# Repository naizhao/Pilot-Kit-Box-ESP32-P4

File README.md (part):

# Pilot Kit Box (ESP32-P4 Edition)

<p align="center">
  <strong>开源低成本飞行数据盒子与态势感知设备 | Open-source low-cost flight data box and situational-awareness device</strong><br>
  官方网站 / Official website: <a href="https://air.club">air.club</a><br>
  网页刷机 / Web flasher: <a href="https://updater.pilotkit.app">updater.pilotkit.app</a>
</p>

**一块扩展板，一整套航空电子**：G1000 风格 PFD、360° 交通雷达、离线
航空地图（机场/导航台/FIX 叠加层）、航空电台收听与录音回放——中英
双语，无需联网；GDL90 数据经蓝牙与 Wi-Fi 对外输出，手机/EFB 无线直连。
**One expansion board, a full avionics suite**: a G1000-style PFD, a 360°
traffic radar, an offline aviation map (airports / navaids / fixes), and an
airband radio with recording playback — bilingual, offline, with GDL90 out
over both Bluetooth and Wi-Fi for phones and EFBs.

- 📶 **1090 + 978 + 航空电台 + GNSS，四路同时收**。SDR 方案只能盯一个频段，
  收了 ADS-B 就没有 UAT、听了电台就丢交通；这里每条链路一颗独立接收机，
  全部并发，互不抢占<br>
  **1090 + 978 + airband + GNSS, all receiving at once.** An SDR watches one
  band at a time — tune ADS-B, lose UAT; listen to the radio, drop traffic.
  Here every link has its own receiver, all concurrent, none blocked
- 📻 **航空电台（118–137 MHz）收听 + 录音回放**。塔台、进近、ATIS、CTAF
  直接出声；飞行中没听清的复述，落地回放重听<br>
  **Airband radio (118–137 MHz) with recording playback.** Tower, approach,
  ATIS and CTAF out loud; replay anything you missed on the ground
- 🧭 **全传感器套装，手持 GPS 都未必有**：IMU 姿态（PFD 地平仪）、气压
  高度与升降率、磁力计、**GPS/北斗/GLONASS/Galileo 四星座 GNSS**
  （内置陶瓷天线 + 外接可切）<br>
  **Full sensor suite, beyond most handheld GPSs**: IMU attitude (PFD
  horizon), barometric altitude and vertical speed, magnetometer, and
  **4-constellation GNSS (GPS/BeiDou/GLONASS/Galileo)** with switchable
  internal patch / external antenna
- 📡 所有数据来自无线电波与板载传感器，实时、真实、零联网——屏幕上的
  每一架飞机、每一条跑道、每一段通话都是本机直接接收解出来的，不是任何
  网络 API 的缓存或转售数据<br>
  Every bit of data comes off the air and onboard sensors — real-time, real,
  zero internet. Every aircraft, runway, and radio call on screen is received
  and decoded by the device itself, not cached from or resold by any online API
- 📶 蓝牙 + Wi-Fi 双通道对外输出：GDL90（Ownship / Traffic / Heartbeat）
  经 BLE 即刻可用，Wi-Fi UDP 输出按同一 GDL90 标准实现中<br>
  Bluetooth + Wi-Fi output: GDL90 (ownship / traffic / heartbeat) ships over
  BLE today; the same GDL90 stream over Wi-Fi UDP is landing next — firmware
  work only, the radio hardware is already on board
- 🛩️ 已与 Garmin Pilot / ForeFlight 等 EFB 配合<br>
  Already works with EFBs such as Garmin Pilot and ForeFlight
- 📼 **飞行轨迹记录**。轨迹与周边飞机数据保存到 SD 卡，dump1090 兼容
  格式，拔卡即读、随时导出；可回放自己的航线与当时的空域，配合
  [Pilot Kit](https://air.club) App 做飞行日志、复盘与分享<br>
  **Flight track logging.** Track and nearby traffic saved to the SD card
  in a dump1090-compatible format — pull the card, read it anywhere.
  Replay your route and the airspace around it, and pair with the
  [Pilot Kit](https://air.club) app for logbooks, review and sharing
- 🖥️ **4.3 寸触摸屏，开机即用**。所有仪表直接画在板上 800×480 屏上，
  触摸切换页面，不需要掏手机就能看全景<br>
  **4.3-inch touchscreen, works out of the box.** Every instrument renders
  on the onboard 800×480 display — the full picture without pulling out a
  phone
- 🔓 全链路开源：固件、KiCad 工程、制造包、字体与数据库管线<br>
  Fully open: firmware, KiCad projects, fabrication packages, font and database pipelines

> ## ⚠️ 免责声明 / Disclaimer
>
> 本设备及其固件为**辅助信息工具**，未取得任何适航认证，**不得用作主用或备用
> 导航设备**，也不得用于正式的飞行活动。所显示的位置、高度、航向、交通、
> 导航台和气象等信息可能延迟、错误或缺失，且随时可能中断。一切飞行决策必须
> 以认证机载设备、官方航图与空管指令为准。使用者自行承担全部风险。
>
> This device and its firmware are an **auxiliary information tool only**.
> They are not airworthiness certified and **must not be used as a primary or
> backup navigation source**, nor in any operational flight activity. Position,
> altitude, heading, traffic, navaid and weather information may be delayed,
> incorrect, or missing, and may stop without warning. All flight decisions
> must be based on certified avionics, official charts, and ATC instructions.
> Use entirely at your own risk.

> **分支 `v4`。** 主机是 **Waveshare ESP32-P4-WIFI6-Touch-LCD-4.3** 一体板：
> ST7701 480×800 MIPI-DSI 面板以 PPA 旋转成 800×480 横屏，GT911 触摸，
> P4NRW32 + ESP32-C6。硬件目标是
> [`hardware/expansion-board-v4/`](hardware/expansion-board-v4/) 的 6 层集成
> 扩展板——以 HAT 方式直插载板 2×20 排母，把 1090/978 接收链、GNSS、IMU、
> 气压计和电源整合到一块板上，**自带 1090 接收链，不再需要 RTL-SDR dongle**。
> 每个硬件版本一个分支；`docs/jlc/lcd-2.4in-8pin/` 与下文 2.4 寸载板内容
> 保留为 v0.8.0 历史 PCB 参考，不代表本分支的当前接线。
>
> **Branch `v4`.** Host board: **Waveshare ESP32-P4-WIFI6-Touch-LCD-4.3**.
> The hardware target is the 6-layer integrated expansion board in
> [`hardware/expansion-board-v4/`](hardware/expansion-board-v4/), which stacks
> onto the carrier's 2×20 header and folds the 1090/978 receive chains, GNSS,
> IMU, barometer, and power onto one board — **no RTL-SDR dongle required**.
> One branch per hardware revision.

## 硬件版本与分支 / Hardware Versions & Branches

项目包含**硬件（扩展板）**与**软件（固件）**两条相互独立的版本线：

- **硬件**按板代走分支：`v1` → `v2` → `v3` → `v4`，每代一个分支；
- **固件**按发布标签走：`v0.5.0` / `v0.6.0` / `v0.8.0`（见 Releases），
  在任何硬件分支上发布，与板代无关。

The project has **two independent version lines**: the **hardware (expansion
boards)** evolves through branches `v1` → `v2` → `v3` → `v4` (one branch per
board generation), while the **firmware** releases via tags `v0.5.0` /
`v0.6.0` / `v0.8.0` (see Releases), cut from whichever hardware branch.

### 四代扩展板 / Four Generations

每个硬件版本一个分支，从旧到新 / One branch per hardware revision, oldest first:

| 分支 Branch | 板子 / Board | EDA | 说明 / Notes |
|---|---|---|---|
| [`v1`](https://github.com/naizhao/Pilot-Kit-Box-ESP32-P4/tree/v1) | 2.4 寸大板：所有模块插在板上，含板载 1090 天线版 / 2.4-inch carrier, all modules plug in, on-board 1090 antenna revision | 嘉立创 EDA | 与 `main` 同源（v0.8.0 时代）/ same lineage as `main` (v0.8.0 era) |
| [`v2`](https://github.com/naizhao/Pilot-Kit-Box-ESP32-P4/tree/v2) | 微雪 4.3 屏配套的 SDR RTL 镂空板 / RTL-SDR cutout board for the Waveshare 4.3 | 嘉立创 EDA | 归档：仅打样 Gerber + 说明，EDA 源不在 git / archive: fabrication Gerbers only, EDA sources not in git |
| [`v3`](https://github.com/naizhao/Pilot-Kit-Box-ESP32-P4/tree/v3) | 脱离 SDR 的完整扩展板（KiCad、expansion-board 命名起点）/ SDR-free integrated expansion board (KiCad, where the expansion-board naming starts) | KiCad | 归档：只维护 v3 硬件，不携带 v4 / archived: v3 hardware only |
| [`v4`](https://github.com/naizhao/Pilot-Kit-Box-ESP32-P4/tree/v4) | v3 + 电源部分 + 布局优化（当前硬件目标）/ v3 plus power section and layout rework (current target) | KiCad | **本分支 / this branch**；公开区只留最终结果 / public tree keeps final results only |

## 项目概览 / Overview

**Pilot Kit Box** 是一个开源、低成本、便携式的飞行数据盒子和航空态势感知设备，可与 [Pilot Kit](https://air.club) 深度结合使用，也可以作为独立设备运行。

如果你熟悉 Stratux、Sentry、Garmin GDL 系列或 uAvionix ping 这类便携式 ADS-B / 飞行数据盒子，可以把 Pilot Kit Box 理解成一个更开放、更低成本、可自己搭建和二次开发的替代方案。它面向飞行员、飞行学员、飞行爱好者以及通航开发者，用常见硬件完成飞行记录、姿态显示、周边交通接收和后续数据分析。

它的核心价值不是单纯“看天上有哪些飞机”，而是帮助用户低成本记录、理解和管理自己的飞行数据。它可以随飞机一起使用，记录每一次飞行中的关键数据，用于飞行日志、回放、分享和分析；也可以接收附近飞机公开广播的 ADS-B / Mode-S 信号，在本机屏幕上显示周边交通信息。

你可以把它理解成一个“飞行员自己的小型数据记录与接收盒子”：它既能独立工作，也能和 Pilot Kit 紧密结合；并已支持通过标准航空数据格式（GDL90 over BLE）与 Garmin Pilot、ForeFlight 等第三方 EFB 软件配合使用。

Pilot Kit Box can work as a standalone device or integrate closely with [Pilot Kit](https://air.club). If you know products such as Stratux, Sentry, Garmin GDL, or uAvionix ping, Pilot Kit Box is best understood as a more open, lower-cost, builder-friendly flight data and ADS-B box. It is intended for pilots, student pilots, aviation enthusiasts, and general-aviation developers who want local flight recording, attitude display, nearby traffic reception, and data they can later review or share.

The main point is not just watching aircraft overhead. Pilot Kit Box is meant to help users record, understand, and manage their own flying at a much lower cost. It can record each flight for logs, replay, sharing, and analysis; it can also receive public ADS-B / Mode-S broadcasts from nearby aircraft and show surrounding traffic on the built-in display.

Think of it as a pilot's own small flight data recorder and receiver: it can run independently, integrate tightly with Pilot Kit, and already speaks standard aviation data (GDL90 over BLE) for third-party EFB apps such as Garmin Pilot and ForeFlight.

## 使用场景 / Use Cases

Pilot Kit Box 的核心用途是：让普通飞行员、飞行学员和飞行爱好者，也能用较低成本拥有一个自己的飞行记录和态势感知盒子。

Pilot Kit Box is designed to give pilots, student pilots, and aviation enthusiasts an affordable personal flight recording and situational-awareness box.

- 记录自己的每一次飞行，为飞行日志、回放、分享和分析提供数据基础。<br>Record each flight as source data for logs, replay, sharing, and analysis.
- 在本机屏幕上显示姿态、航向、高度、速度、垂直速度等飞行状态信息。<br>Display flight state such as attitude, heading, altitude, speed, and vertical speed on the local screen.
- 接收附近飞机的 ADS-B / Mode-S 广播，显示周边交通、航班号、国家、航司、机型和注册号等信息。<br>Receive nearby ADS-B / Mode-S traffic and show callsign, country, airline, aircraft type, and registration when known.
- 在没有互联网的情况下，本地接收和记录航空数据，而不是依赖在线航班网站。<br>Receive and record aviation data locally without relying on online flight-tracking websites.
- 与 Pilot Kit 软件结合，把硬件采集到的数据用于更完整的飞行记录、回放、分析和分享体验。<br>Use captured device data with Pilot Kit for richer flight records, replay, analysis, and sharing.
- 作为通用飞行数据盒子继续扩展；GDL90 已通过 BLE 输出（Ownship / Traffic / Heartbeat / Raw），Wi-Fi GDL90 在路线图中，目标是连接 Garmin Pilot、ForeFlight 等 EFB。<br>Continue evolving as a general-purpose flight data box; GDL90 already ships over BLE (ownship / traffic / heartbeat / raw), with Wi-Fi GDL90 on the roadmap targeting EFBs such as Garmin Pilot and ForeFlight.
- 给通航、航电、嵌入式和 SDR 爱好者提供一个完整、开源、可学习的参考实现。<br>Provide a complete open-source reference for general aviation, avionics, embedded systems, and SDR builders.

## 为什么要做这个设备 / Why Build This

市面上已经有 Stratux、Sentry、Garmin GDL、uAvionix ping 等便携式 ADS-B 接收器、飞行记录盒子和通航辅助设备，但很多产品要么价格较高，要么生态相对封闭，要么不方便用户理解、修改和扩展内部的数据链路。

Pilot Kit Box 想解决的是这个问题：

- **低成本**：用 ESP32-P4、v3/v4 扩展板（自带 1090 接收链，无需 RTL-SDR dongle）、屏幕、IMU 和常见电源模块，做出一个普通用户也能负担的飞行数据盒子。
- **通用性**：它不是只能配合某一个 App 使用的封闭硬件；它可以独立使用，也可以面向标准航空数据接口继续扩展。
- **与 Pilot Kit 紧密结合**：Pilot Kit 可以充分利用 Box 采集的数据，提供更完整的飞行记录、回放、分析和分享能力。
- **本地记录**：飞行数据可以在设备本地记录，为飞行复盘和个人飞行档案提供基础。
- **态势感知**：除了记录自己的飞行，也能接收附近 ADS-B / Mode-S 交通，帮助理解周边空域情况。
- **开源透明**：从 SDR 接收、ADS-B 解码、状态聚合、屏幕显示到数据库维护，整个链路都可以检查、修改和复现。
- **可继续扩展**：它可以是一个低成本替代方案，也可以作为移动端、云端分析、EFB 集成、Wi-Fi GDL90 输出和硬件外壳迭代的平台。

Portable ADS-B receivers and flight data boxes already exist, including Stratux, Sentry, Garmin GDL, and uAvionix ping. Many of them are effective products, but they can be expensive, relatively closed, or hard for users to inspect, modify, and extend.

Pilot Kit Box focuses on:

- **Low cost**: ESP32-P4, the v3/v4 expansion board (its own 1090 MHz receive chain — no RTL-SDR dongle), display, IMU, and common power modules keep the hardware approachable.
- **General-purpose use**: it is not locked to one app; it can run on its own and already speaks standard aviation data interfaces (GDL90).
- **Tight Pilot Kit integration**: Pilot Kit can use Box data for richer flight records, replay, analysis, and sharing.
- **Local recording**: flight data can be recorded on the device for review and personal archives.
- **Situational awareness**: the same box can receive nearby ADS-B / Mode-S traffic and help users understand surrounding airspace.
- **Open implementation**: SDR reception, ADS-B decoding, state fusion, display rendering, and database maintenance are all inspectable and reproducible.
- **Room to grow**: it can be a low-cost alternative today and a platform for mobile apps, cloud analysis, EFB integration, Wi-Fi GDL90 output, and enclosure iterations later.

## 技术概览 / Technical Overview

当前 ESP32-P4 版本把传统依赖 Linux 板卡的 ADS-B 接收链路压缩到单片机 + RTOS 架构。1090 MHz 接收由 **v3/v4 扩展板**完成：板载接收链（QPL9547 LNA + TA0970A SAW + AD8313 对数检波 + TLV3501 比较器）把脉冲馈给 RP2040，RP2040 以 PIO+DMA 捕获双沿、重建 56/112-bit Mode-S 帧，再经 921600 UART 送 ESP32-P4 做 CRC 过滤、CPR 定位融合、飞机状态聚合，并通过 BLE GATT、串口以及 LittleFS / MicroSD 文件输出给移动端或调试工具。（早期 v1/v2 载板走 P4 原生 USB 2.0 HS 驱动 RTL-SDR dongle 的路径已退役，固件与组件树均不再包含该代码。）

The ESP32-P4 edition removes the Linux SBC from the ADS-B path. The 1090 MHz receive chain lives on the **v3/v4 expansion boards**: the onboard chain (QPL9547 LNA + TA0970A SAW + AD8313 log detector + TLV3501 comparator) feeds pulses to an RP2040, which captures dual edges via PIO+DMA, rebuilds 56/112-bit Mode S frames, and ships them to the ESP32-P4 over a 921600-baud UART for CRC filtering, CPR position fusion, and per-aircraft state aggregation, published over BLE GATT, serial output, and LittleFS or MicroSD logs. (The early v1/v2-carrier path — the P4 driving an RTL-SDR dongle over native USB 2.0 HS — is retired; neither the firmware nor the component tree still carries it.)

## 安全与适航边界 / Safety And Certification Boundary

Pilot Kit Box 是开源原型和态势感知设备，当前仓库没有 FAA、EASA、CAAC 或其他适航/TSO 认证。它不能作为主飞行仪表、备用飞行仪表、导航源或防撞系统使用；任何飞行决策必须以认证航电、机载仪表、目视观察和适用法规为准。

Pilot Kit Box is an open-source prototype and situational-awareness device. This repository does not represent FAA, EASA, CAAC, TSO, or other airworthiness certification. Do not use it as a primary flight instrument, backup flight instrument, navigation source, or collision-avoidance system; flight decisions must remain based on certified avionics, installed instruments, visual scan, and applicable regulations.

## 当前状态 / Current Status

截至 **2026-10-15**，当前 4.3 寸固件已经覆盖 ADS-B 接收与解码、BLE
GDL90 分发、GPS 定位与两段式授时（`pk_clock`：BLE 粗校 + GPS fix 精校）、
BMP388 气压高度、LittleFS/MicroSD 记录、ST7701 MIPI-DSI 横屏显示、
GT911 触摸导航、交通雷达、ADS-B 列表、离线地图（microSD pmtiles 底图 +
机场/导航台/FIX 航空叠加层）、航空电台（Airband）收听与录音回放（ES8311
音频输出）、实时诊断、本地航空识别数据库和 BNO085 姿态融合。

As of **2026-10-15**, the current 4.3-inch firmware includes ADS-B reception
and decode, BLE GDL90 distribution, GPS positioning and two-stage time
discipline (`pk_clock`: BLE coarse sync + GPS fine sync after fix), BMP388
barometric altitude, LittleFS/MicroSD recording, an ST7701 MIPI-DSI
landscape display, GT911 touch navigation, traffic radar, an ADS-B list,
the offline map (microSD pmtiles basemap plus airport/navaid/FIX overlay),
an airband radio with recording playback (ES8311 audio output), live
diagnostics, local aviation identity databases, and BNO085 attitude fusion.

### `v0.8.0` 发布重点 / Release Highlights

- 新增 360° 交通雷达、PFD HSI 前方交通叠加和统一 own-ship 航向决策。<br>Adds the 360-degree traffic radar, forward-traffic HSI overlay, and unified own-ship heading selection.
- 新增 BMP388 气压高度/升降率、可调 QNH，以及可滚动实时 DIAG 页面。<br>Adds BMP388 altitude/vertical speed, adjustable QNH, and the scrollable live DIAG page.
- 增强 GT-U8 GPS/北斗诊断和 RMC 授时，并通过 BLE 输出 GDL90 Ownship Report；GPIO50 PPS 已被固件消费，用于时间锁定判定（fix 有效 + PPS <2 s + NMEA <5 s）。<br>Expands GT-U8 GPS/BeiDou diagnostics, RMC time sync, and BLE GDL90 Ownship Report output; GPIO50 PPS is consumed for the time-lock status (valid fix + PPS <2 s + NMEA <5 s).
- 新增 MicroSD 探测、Flash/MicroSD 日志切换、约 1 GiB 轮转保留和受保护格式化。<br>Adds MicroSD detection, Flash/MicroSD log selection, about 1 GiB rotation retention, and guarded formatting.
- 完成 2.4 寸载板、板载 1090 MHz IFA 天线、3D 打印外壳和面板原型实物验证。<br>Documents the fabricated 2.4-inch carrier, on-board 1090 MHz IFA antenna, printed enclosure, and faceplate prototype.

## 核心特性 / Features

| 功能 | Feature | 状态 / Status |
|---|---|---|
| ESP32-P4 + FreeRTOS 固件，无 Linux 启动链路 | ESP32-P4 + FreeRTOS firmware, no Linux boot chain | 已实现 / Implemented |
| RP2040 拓展板双沿捕获 1090 MHz ADS-B，921600 UART 送 P4 解码（USB RTL-SDR 路径已退役） | RP2040 add-on dual-edge capture of 1090 MHz ADS-B, raw frames to the P4 over 921600-baud UART (USB RTL-SDR path retired) | 已实现 / Implemented |
| `adsb_lnk` 任务：921600 UART 收 RP2040 帧、CRC 过滤后进 CPR/融合与记录链 | `adsb_lnk` task: RP2040 frames over 921600-baud UART, CRC-filtered into the CPR/fusion and recording chain | 已实现 / Implemented |
| dump1090 派生 Mode-S 解码、CRC 过滤、CPR 全球定位 | dump1090-derived Mode-S decode, CRC filtering, CPR global position decode | 已实现 / Implemented |
| 最多同时跟踪 64 个 ADS-B / Mode-S 目标，并聚合呼号、高度、位置、速度、垂直速度、应答机码和机型信息 | Tracks up to 64 ADS-B / Mode-S targets at once, aggregating callsign, altitude, position, velocity, vertical rate, squawk, and aircraft type | 已实现 / Implemented |
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
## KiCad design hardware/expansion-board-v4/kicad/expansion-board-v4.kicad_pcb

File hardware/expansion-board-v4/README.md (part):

# Pilot Kit Avionics Board V4.11

**Integrated ADS-B / GNSS / IMU expansion board for the Pilot Kit Box**
集成 ADS-B / GNSS / IMU 扩展板

A 6-layer, 100.1 × 62.1 mm HAT that stacks onto the Waveshare
ESP32-P4-WIFI6-Touch-LCD-4.3 carrier's 2×20 header. It replaces the four
discrete modules used by the current prototype (RTL-SDR dongle, BNO085,
GT-U8 GNSS, BMP388) with a single board — **including its own 1090 MHz
receive chain, so no RTL-SDR dongle is required.**

6 层、100.1 × 62.1 mm，以 HAT 方式直插微雪 ESP32-P4-WIFI6-Touch-LCD-4.3
载板的 2×20 排母，把现有原型的四个分立模块（RTL-SDR dongle、BNO085、
GT-U8 GNSS、BMP388）整合成一块板，**自带 1090 MHz 接收链，不再需要 dongle**。

---

## ⚠️ Status / 当前状态

> **V4.10 hardware has been powered and tested; V4.11 is the current design.**
> V4.11 adds the validated SW3 sensing ECO: `J1.14` / ESP32-P4 `GPIO4` reaches
> `CHG_QON` through `R67` (1 kΩ) and `D10` (1N4148WS), while SW3 remains directly
> connected to the SY6970 `/QON` input for battery-only hardware wake. The diode
> isolates the charger's ~3.56 V `/QON` pull-up from the 3.3 V GPIO domain.
>
> V4.9 introduced `J11`, the board's single debug connector. Before it there was **no way
> to reach the CC1312R's cJTAG pins** — `SUBG_TMSC`/`SUBG_TCKC`/`SUBG_RESET` ran
> point-to-point between `U8` (RP2040) and `U10`, with nowhere to break the link or land
> a probe, so "ROM SSI and cJTAG both unresponsive" could not be attributed to either
> side. `J11` breaks all three out and also replaces the former `TP1`–`TP7` test pads and
> the `SW1`/`SW2` solder jumpers (all nine removed).
>
> V4.10 changes `J11` itself, in two ways that will make a V4.9-era diagram misleading:
> it is now a **2x10 bare-pad array, not a 2x8 header** (twenty φ1.0 mm pads on a
> 2.54 mm grid, nothing fitted, mating with a 2x10p PCB test clip), and **every pin
> number shifted by four** — V4.9 pins 1–16 are now pins 5–20. With no header there are
> no jumper caps either: bridge 5-6 = reset, 7-8 = BOOTSEL, 19-20 = self-test loopback
> (remove `R57` first) with tweezers or a solder blob. A 20-entry pin map is printed on
> the bottom silkscreen.
>
> The four airband nets on pins 1–4 are routed along the bottom of the board, clear of
> the 1090 MHz front end (0.0 mm of copper in the y 50.5–58 band). Pin 1 carries the
> 26 MHz reference through **`R66`, a 0 R link that is not fitted by default**: its
> 120 mm branch would otherwise add ~17 pF to a TCXO whose datasheet load budget is
> 10 pF ±10 %, and an under-driven reference means airband receives nothing. Solder the
> 0 R only while probing.
> V4.8 added a permanently-powered backup rail for the GNSS module's VBAT pin
> (`U23` LDO off `BAT_P` -> `3V3_BKP` -> `D7` -> `GNSS_VBAT`, plus the `BT1`
> MS621FE-FL11E rechargeable cell through `R63`), so the module keeps its RTC
> and ephemeris across power-off instead of cold-starting on every boot.
> V4.8 also adds the board's first two status LEDs — `D8` power (on 3V3_DIG,
> extinguishes by itself at power-off) and `D9` charge, driven directly by the
> SY6970 open-drain `STAT` pin (lit while charging, off when done, **blinking at
> 1 Hz on any charge fault**). Neither consumes a GPIO; `R64`/`R65` limit both to
> about 1 mA. They sit on the X+ wall between the USB-C receptacle and the power
> button, so the enclosure needs a matching opening on that wall.
> V4.7 added a hardware power button (`SW3` on the SY6970 `/QON` pin;
> BATFET reset requires battery-only operation) and the airband
> reference-clock DC-block (`C99` + `R61`). V4.6 added the 118–137 MHz airband
> receive chain (BK4819 + 26 MHz TCXO + PCM1808 I²S capture, stage G of the
> assembly list). V4.5 carried forward the
> V4.3 electrical corrections and the V4.0 measured 50.0mm IFA geometry, and
> fixed GNSS active-antenna detection: the module's `VCC_RF` (U7.14) now feeds
> the two bias-tee PMOS sources instead of being left unconnected, so `$GPTXT`
> can report `ANTENNA OK/OPEN/SHORT`. Current V4.11 DRC has 0 unconnected and
> 0 copper findings, with two retained D9 silkscreen overlaps; ERC remains
> 0 errors / 10 warnings. The V4.10 SW3 flywire closed-loop is complete; airband
> RF performance still needs bench validation. The existing 3.3 V supply to Y4 is accepted for this prototype; U22 VREF now has C100 (100 nF / 0603) in parallel with C92 (10 µF). Owners of V4.0 boards must follow the
> internal rework record before powering the 1090 MHz chain.
>
> **V4.10 实板已上电并完成电源键飞线验证；V4.11 是当前设计版本。**
> V4.11 固化该 SW3 感知 ECO：`J1.14` / ESP32-P4 `GPIO4` 经 `R67`（1kΩ）和
> `D10`（1N4148WS）单向感知 `CHG_QON`，SW3 仍直接连接 SY6970 `/QON`，保留
> 仅电池关机后的硬件唤醒；二极管隔离 `/QON` 实测约 3.56V 的内部上拉与 3.3V GPIO 域。
>
> V4.9 引入了 `J11` 这个全板唯一的调试口。在此之前**板上没有任何办法接触 CC1312R
> 的 cJTAG**：`SUBG_TMSC`/`SUBG_TCKC`/`SUBG_RESET` 在 `U8`(RP2040) 与 `U10` 之间
> 点对点直连，中途既不能断开也无处下探针，「ROM SSI 与 cJTAG 同时无响应」时无法
> 归因到哪一侧。`J11` 把三根引出，并取代原 `TP1`~`TP7` 与 `SW1`/`SW2`（九个已删除）。
>
> V4.10 改的是 `J11` 本身，两处都会让照 V4.9 的图读板的人读错：它现在是
> **2x10 裸焊盘阵列，不是 2x8 排针**（20 个 φ1.0mm 圆盘，2.54mm 网格，不贴任何件，
> 配 2x10p PCB 测试夹），而且**脚号整体后移 4 位**——V4.9 的 pin1~16 现在是 pin5~20。
> 没有排针也就没有跳线帽：三对短接改用镊子或锡桥，5-6 = 复位、7-8 = BOOTSEL、
> 19-20 = 自检回环（需先拆 `R57`）。B 面丝印印了 20 格对照表。
>
> airband 四脚已沿板子下缘布通，完全避开 1090 前端（y 50.5~58 带内铜长 0.0mm）。
> pin1 的 26MHz 参考经 **`R66`（0Ω，默认不贴）** 引出：那根 120mm 分支直连会给 TCXO
> 加约 17pF，而手册负载预算只有 10pF ±10%，参考幅度不够则 airband 整条收不了。
> 只在探测时手焊 0Ω，用完拆掉。
> V4.8 = V4.7 + GNSS 模块 VBAT 常供电
> （`U23` LDO 取自 `BAT_P` -> `3V3_BKP` -> `D7` -> `GNSS_VBAT`，并经 `R63` 挂 `BT1`
> MS621FE-FL11E 可充电电池）：模块关机后保住 RTC 与星历，不再每次开机冷启动。
> V4.8 另有全板第一次出现的两颗指示灯：`D8` 电源（接 3V3_DIG，关机自灭）、
> `D9` 充电（直接由 SY6970 的开漏 `STAT` 脚驱动：充电中亮、充满灭、
> **充电故障时 1Hz 闪**）。两颗都不占 GPIO，`R64`/`R65` 限流到约 1mA。
> 位置在 X+ 壁的 USB-C 口与电源键之间，外壳需在该壁配套开孔。
> V4.7 = V4.6 + 硬件电源键
> （`SW3` 接 SY6970 的 `/QON`；BATFET 复位有仅电池供电的条件）
> + 航空波段参考时钟的隔直（`C99` + `R61`）。V4.6 = V4.5 + 118–137MHz 航空波段接收
> （BK4819 + 26MHz TCXO + PCM1808 I²S 采集，对应贴片清单阶段 G）。V4.5 继承 V4.3 的
> 电气修正和 V4.0 逐刀实测定型的 50.0mm IFA 几何，并修复 GNSS 有源天线检测：模块
> `VCC_RF`(U7.14) 不再悬空，改为两路偏置 Tee PMOS 的源极电源，模块据此才能输出
> `ANTENNA OK/OPEN/SHORT`。当前 V4.11 DRC 未连通 0 / 铜 0，保留 2 个 D9 丝印重叠；
> ERC 0 error / 10 warning。V4.10 SW3 飞线实物闭环已完成，航空波段 RF 性能仍待台架验证；
> 用户接受本轮样板保留 Y4 的3.3V供电，回板验证；U22 VREF 已增加 C100（100nF／0603），与 C92（10µF）并联。
> V4.0 实物在开启 1090 MHz 链路前必须先按内部返修记录处理。

| | Status / 状态 |
|---|---|
| Schematic / 原理图 | ✅ Complete / 完成 |
| Layout & routing / 布局布线 | ✅ Complete — unconnected 0, copper 0; 2 known D9 silkscreen overlaps / 未连通 0、铜 0；已知 D9 丝印重叠 2 |
| Manufacturing files / 制造文件 | ✅ Gerber + drill export cleanly / 可正常导出 |
| **Fabrication / 打样** | ⚠️ V4.10 fabricated; V4.11 is the SW3 ECO spin / V4.10 已打样，V4.11 为 SW3 ECO 新版 |
| **Bring-up / 上电验证** | ✅ V4.10 SW3 ECO validated by flywire; V4.11 PCB pending / V4.10 飞线已验证，V4.11 新板待回板 |
| **Debug access / 可测性** | ⚠️ `J11` 2x10 bare-pad array (V4.10), 20 signals incl. airband; never used on hardware / `J11` 2x10 裸焊盘阵列（V4.10），20 路含 airband，未实板验证 |
| **Airband RX / 航空波段接收** | ⚠️ New in V4.6, never fabricated or bench-tested / V4.6 新增，未打样未台架验证 |
| **Power button / 电源键** | ✅ Battery-only wake and GPIO short/long press validated on V4.10 flywire; frozen in V4.11 / 仅电池唤醒与 GPIO 短长按已在 V4.10 飞线验证，V4.11 已固化 |
| **On-board IFA antenna / 板载 IFA 天线** | ✅ V4.0 per-cut measured 50.0mm geometry transferred / V4.0 逐刀实测 50.0mm 几何已回灌 |

**About the IFA antenna** — V4.7 keeps the V4.0 physical-board result: a
**50.0mm copper outer envelope** (48.5mm radiating-arm centerline span), with
the matching network straight-through (`ZS1`=0R, `ZP1`/`ZP2`=DNP). The V4.0
board was trimmed cut-by-cut from 53.5mm and stopped at 50.0mm, where it
measured **1082.5MHz, SWR 1.09, 45+j0.5Ω** in the case with the battery
fitted. The same series yields a slope of **24–25 MHz/mm**. These values
validate the transferred geometry, but each new enclosure/material batch
still needs a VNA spot check. See [`BOM_IFA_TUNING.md`](BOM_IFA_TUNING.md).

板载 1090MHz 倒 F 天线采用 V4.0 实板逐刀定型结果：**铜箔外包络 50.0mm**（辐射臂
中心线跨度 48.5mm），匹配网络直通（`ZS1`=0R、`ZP1`/`ZP2`=DNP）。该板由 53.5mm
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
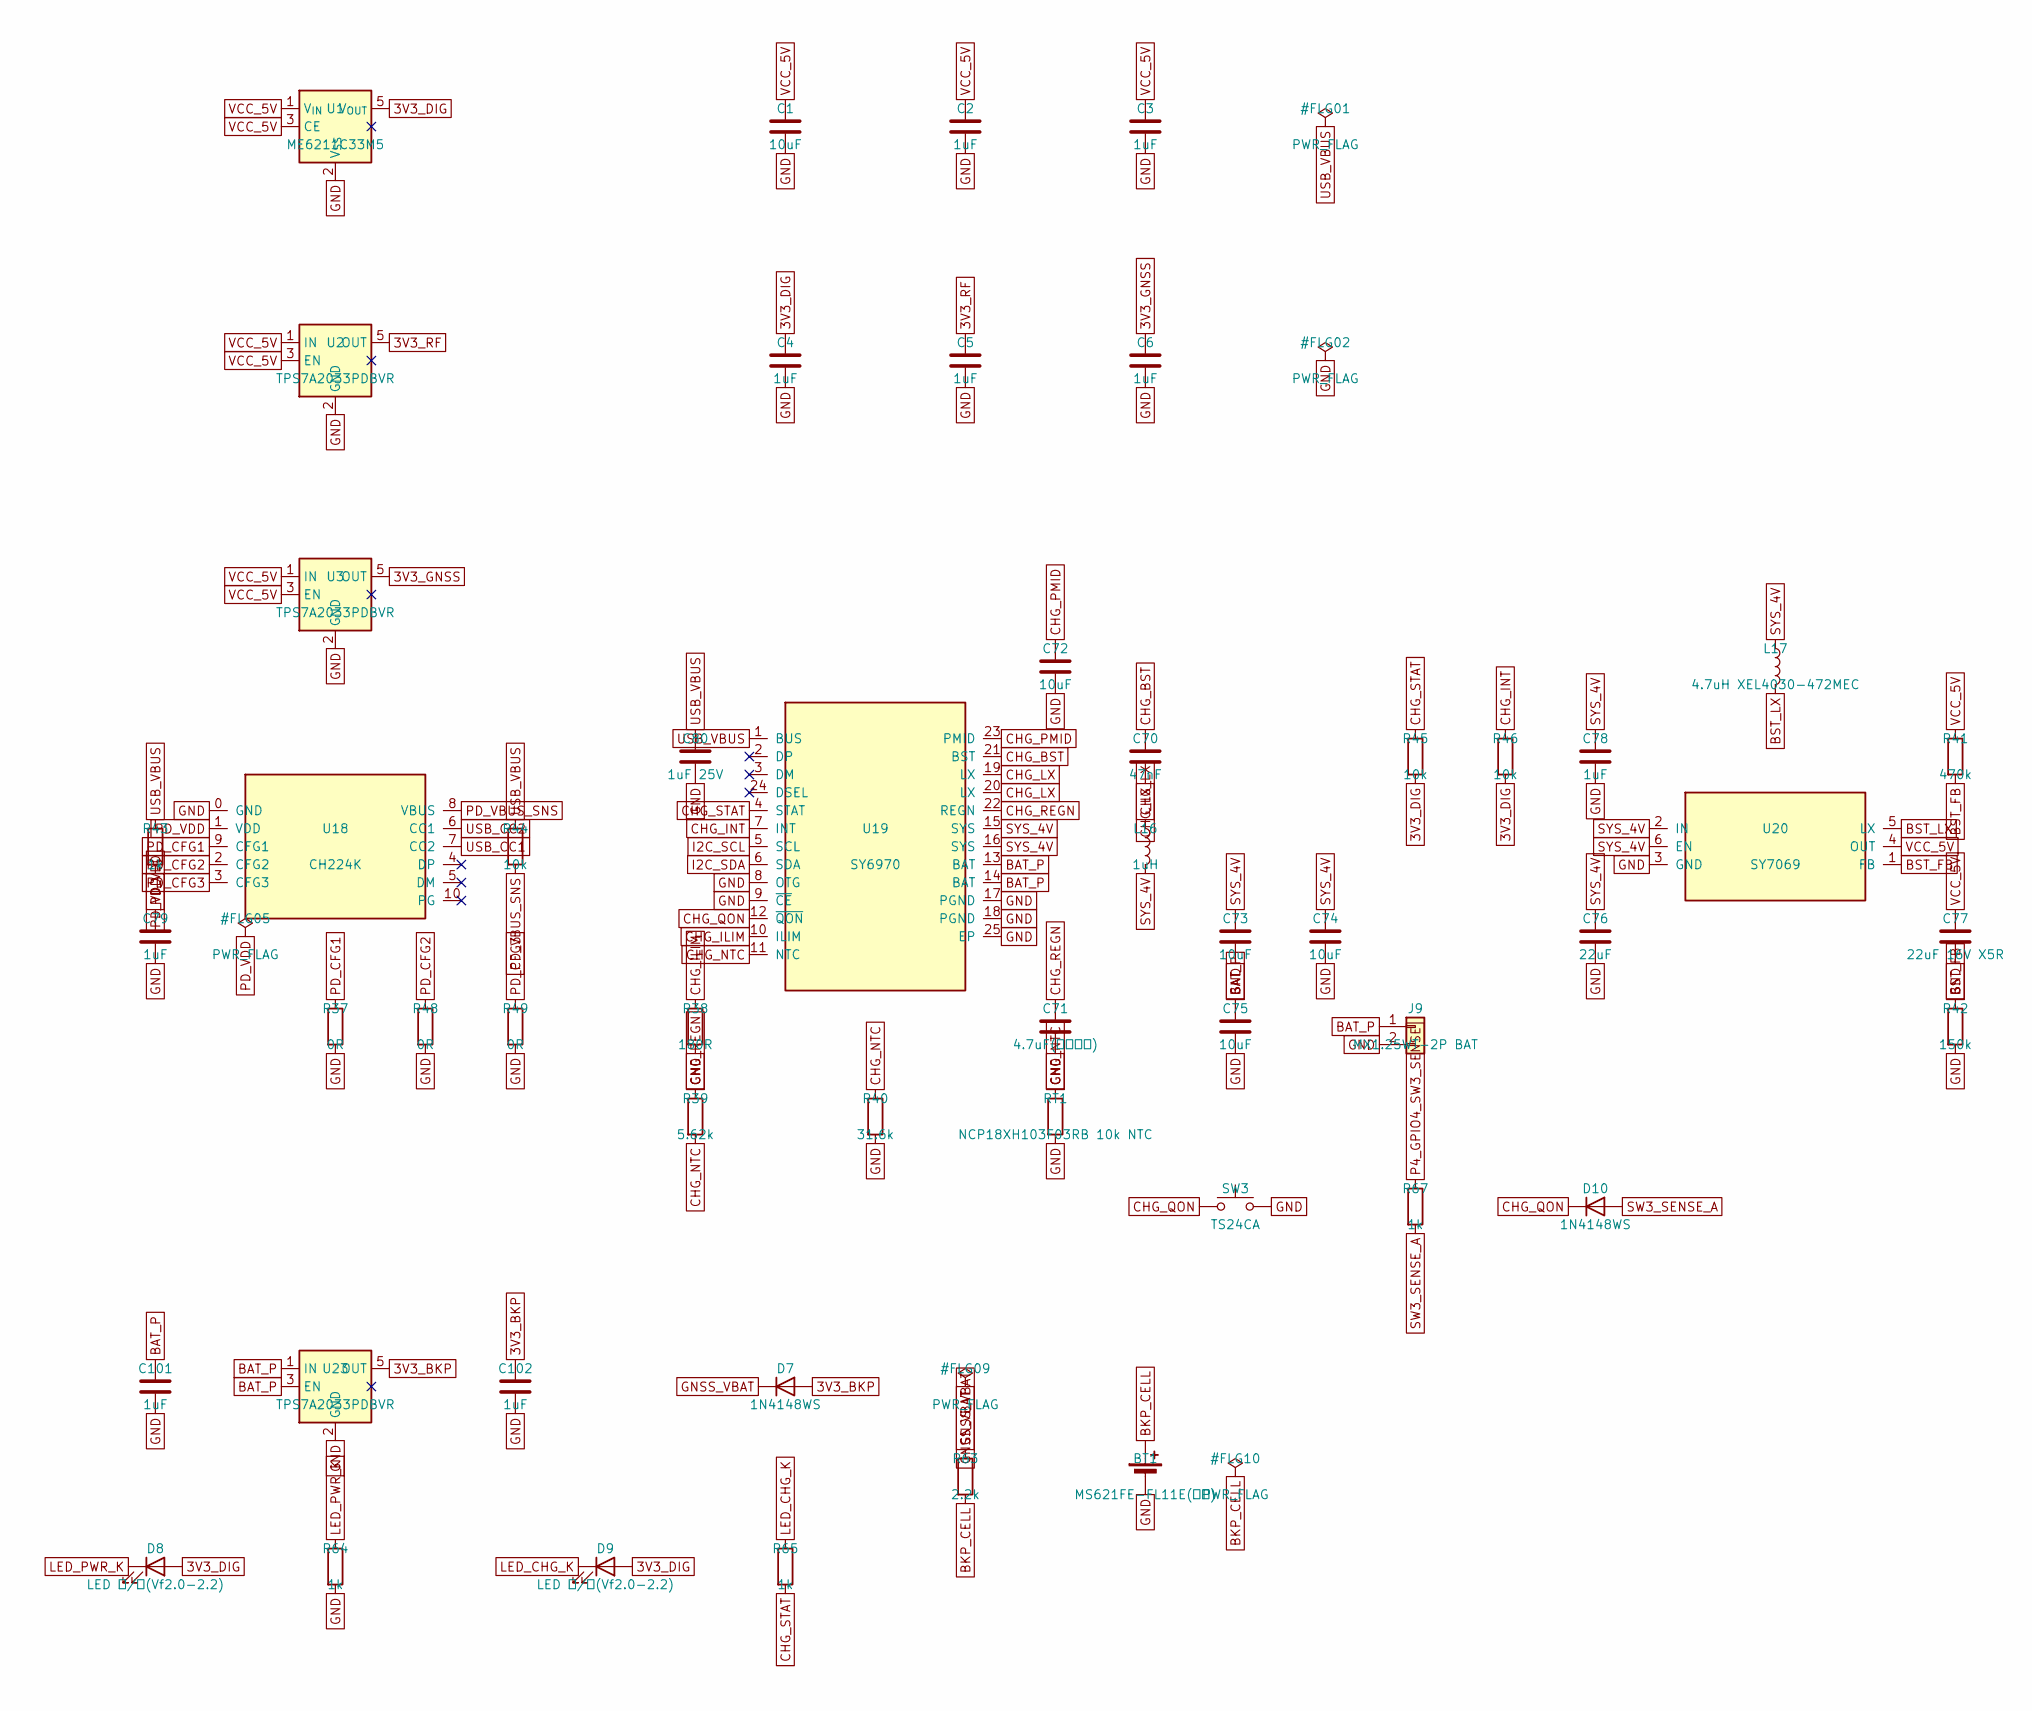
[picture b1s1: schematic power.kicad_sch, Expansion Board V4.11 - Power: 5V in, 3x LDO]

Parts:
BT1: MS621FE-FL11E(选贴); MS621FE-FL11E
C1, C73, C74, C75: 10uF; C_0805_2012Metric
C2, C3, C4, C6, C78, C79, C101, C102: 1uF; C_0603_1608Metric
C5: 1uF; C_0402_1005Metric
C70: 47nF; C_0603_1608Metric
C71: 4.7uF(带电源版); C_0603_1608Metric
C72: 10uF; C_1206_3216Metric
C76: 22uF; C_1206_3216Metric
C77: 22uF 16V X5R; C_1206_3216Metric
C80: 1uF 25V; C_0603_1608Metric
D7, D10: 1N4148WS; D_SOD-323
D8, D9: LED 红/黄(Vf2.0-2.2); LED_0805_2012Metric
J9: MX1.25WT-2P BAT; MX1.25WT-2P_1x02-1MP_P1.25mm_Horizontal
L16: 1uH; L_Bourns-SRN4018
L17: 4.7uH XEL4030-472MEC; L_Coilcraft_XxL4030
R37, R48, R49: 0R; R_0603_1608Metric
R38: 180R; R_0603_1608Metric
R39: 5.62k; R_0603_1608Metric
R40: 31.6k; R_0603_1608Metric
R41: 470k; R_0603_1608Metric
R42: 150k; R_0603_1608Metric
R43, R64, R65, R67: 1k; R_0603_1608Metric
R44, R45, R46: 10k; R_0603_1608Metric
R63: 2.2k; R_0603_1608Metric
RT1: NCP18XH103F03RB 10k NTC; R_0603_1608Metric
SW3: TS24CA; SW_TS24CA_2x4_SideAct
U1: ME6211C33M5; SOT-23-5
U2, U3, U23: TPS7A2033PDBVR; SOT-23-5
U18: CH224K; CH224K_ESSOP-10
U19: SY6970; QFN-24-1EP_4x4mm_P0.5mm_EP2.6x2.6mm_ThermalVias
U20: SY7069; TSOT-23-6

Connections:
3V3_BKP: C102.1, D7.2 (A), U23.5 (OUT)
3V3_DIG: C4.1, D8.2 (A), D9.2 (A), R45.2, R46.2, U1.5 (V_{OUT}); also elsewhere on the board
3V3_GNSS: C6.1, U3.5 (OUT); also elsewhere on the board
3V3_RF: C5.1, U2.5 (OUT); also elsewhere on the board
BAT_P: C75.1, C101.1, J9.1, U19.13 (BAT), U19.14 (BAT), U23.1 (IN), U23.3 (EN)
BKP_CELL: BT1.1 (+), R63.2
BST_FB: R41.2, R42.1, U20.1 (FB)
BST_LX: L17.2, U20.5 (LX)
CHG_BST: C70.1, U19.21 (BST)
CHG_ILIM: R38.1, U19.10 (ILIM)
CHG_INT: R46.1, U19.7 (INT)
CHG_LX: C70.2, L16.1, U19.19 (LX), U19.20 (LX)
CHG_NTC: R39.2, R40.1, RT1.1, U19.11 (NTC)
CHG_PMID: C72.1, U19.23 (PMID)
CHG_QON: D10.1 (K), SW3.1, U19.12 (~QON)
CHG_REGN: C71.1, R39.1, U19.22 (REGN)
CHG_STAT: R45.1, R65.2, U19.4 (STAT)
GND: BT1.2 (-), C1.2, C2.2, C3.2, C4.2, C5.2, C6.2, C71.2, C72.2, C73.2, C74.2, C75.2, C76.2, C77.2, C78.2, C79.2, C80.2, C101.2, C102.2, J9.2, R37.2, R38.2, R40.2, R42.2, R48.2, R49.2, R64.2, RT1.2, SW3.2, U1.2 (V_{SS}), U2.2 (GND), U3.2 (GND), U18.0 (GND), U19.8 (OTG), U19.9 (~CE), U19.17 (PGND), U19.18 (PGND), U19.25 (EP), U20.3 (GND), U23.2 (GND); also elsewhere on the board
GNSS_VBAT: D7.1 (K), R63.1; also elsewhere on the board
I2C_SCL: U19.5 (SCL); also elsewhere on the board
I2C_SDA: U19.6 (SDA); also elsewhere on the board
LED_CHG_K: D9.1 (K), R65.1
LED_PWR_K: D8.1 (K), R64.1
P4_GPIO4_SW3_SENSE: R67.1; also elsewhere on the board
PD_CFG1: R37.1, U18.9 (CFG1)
PD_CFG2: R48.1, U18.2 (CFG2)
PD_CFG3: R49.1, U18.3 (CFG3)
PD_VBUS_SNS: R44.2, U18.8 (VBUS)
PD_VDD: C79.1, R43.2, U18.1 (VDD)
SW3_SENSE_A: D10.2 (A), R67.2
SYS_4V: C73.1, C74.1, C76.1, C78.1, L16.2, L17.1, U19.15 (SYS), U19.16 (SYS), U20.2 (IN), U20.6 (EN)
USB_CC1: U18.7 (CC2); also elsewhere on the board
USB_CC2: U18.6 (CC1); also elsewhere on the board
USB_VBUS: C80.1, R43.1, R44.1, U19.1 (BUS); also elsewhere on the board
VCC_5V: C1.1, C2.1, C3.1, C77.1, R41.1, U1.1 (V_{IN}), U1.3 (CE), U2.1 (IN), U2.3 (EN), U3.1 (IN), U3.3 (EN), U20.4 (OUT); also elsewhere on the board

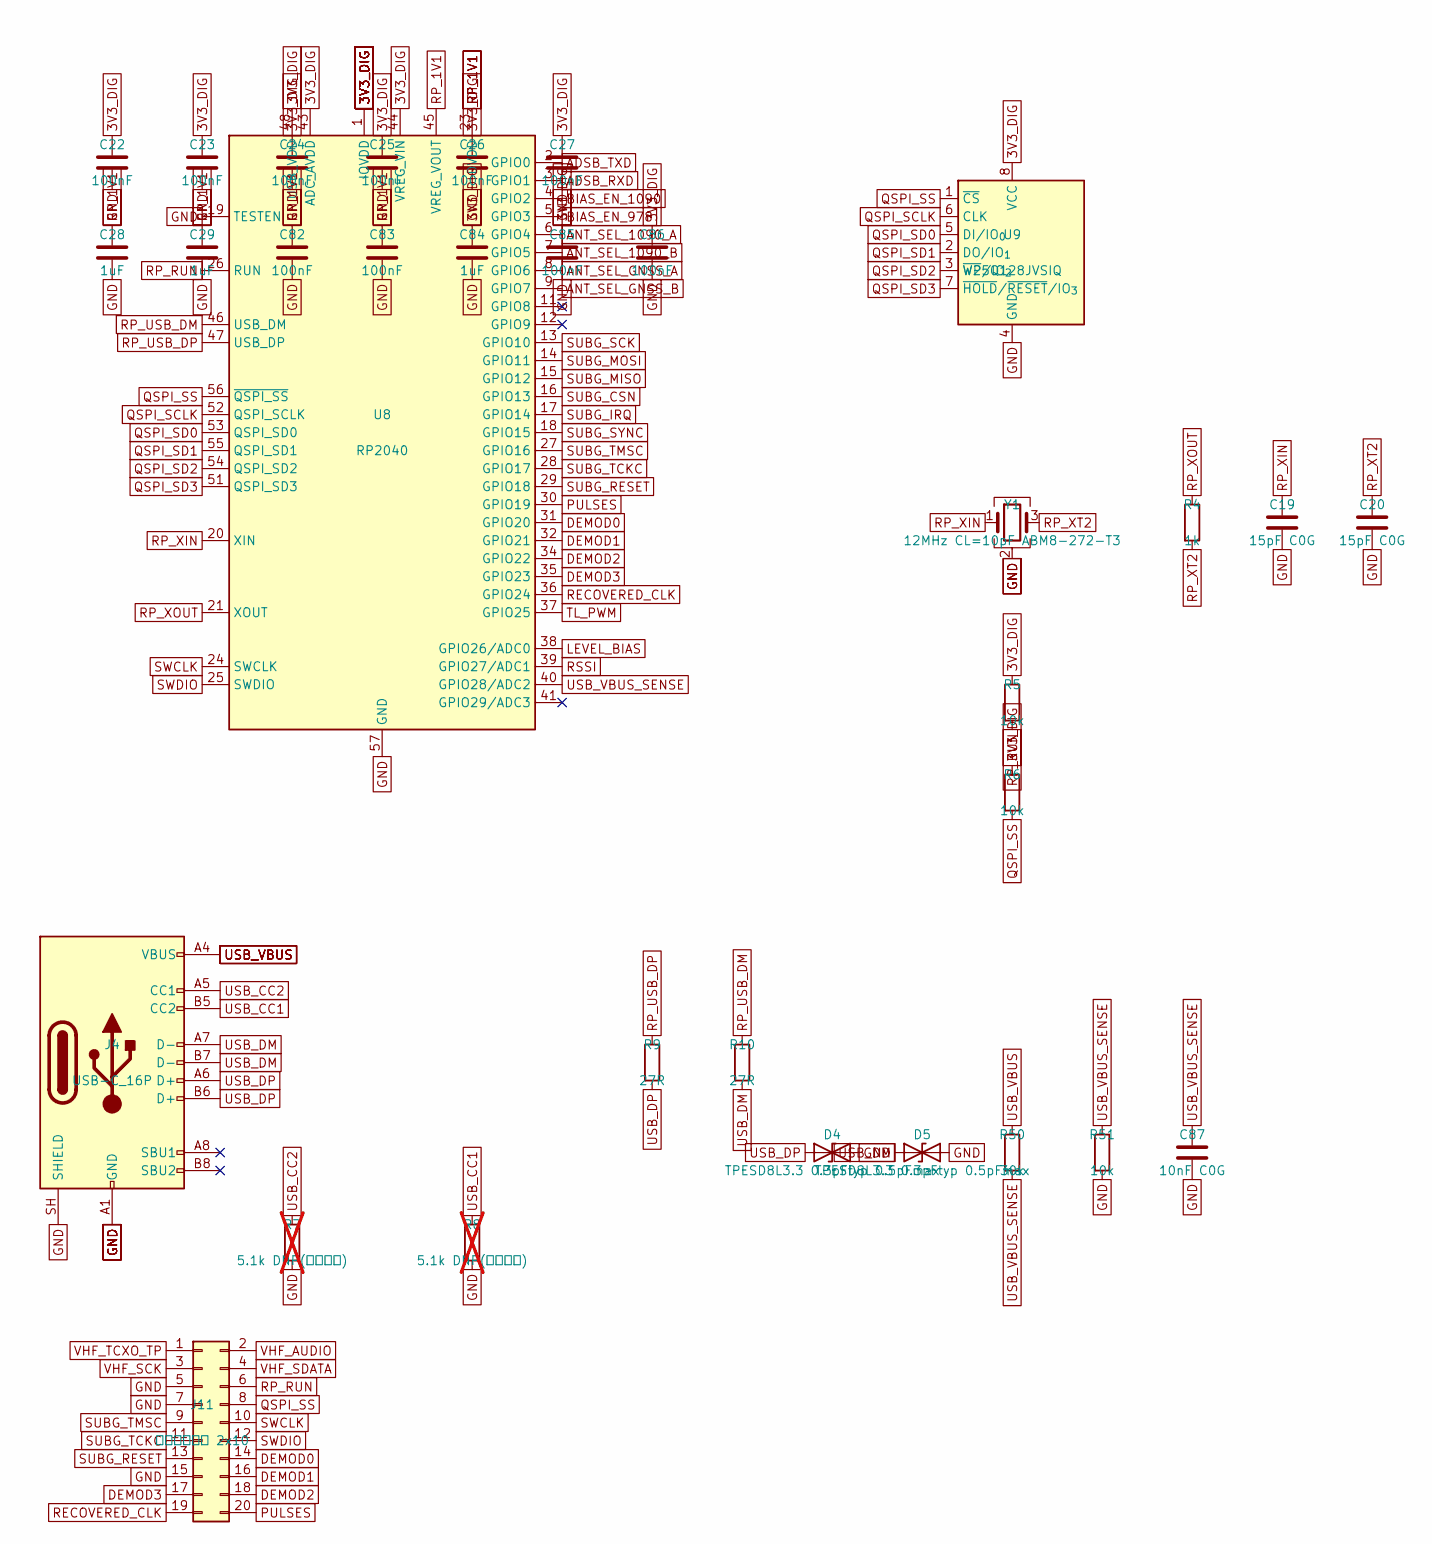
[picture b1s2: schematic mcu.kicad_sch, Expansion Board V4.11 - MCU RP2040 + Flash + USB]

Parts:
C19, C20: 15pF C0G; C_0603_1608Metric
C22, C23, C24, C25, C26, C27, C82, C83, C85, C86: 100nF; C_0603_1608Metric
C28, C29, C84: 1uF; C_0603_1608Metric
C87: 10nF C0G; C_0603_1608Metric
D4, D5: TPESD8L3.3 0.3pFtyp 0.5pFmax; D_0402_1005Metric
J4: USB-C_16P; USB_C_Receptacle_HRO_TYPE-C-31-M-12
J11: 调试焊盘阵列 2x10; TestPad_2x10_P2.54mm
R4: 1k; R_0603_1608Metric
R5, R6, R51: 10k; R_0603_1608Metric
R7, R8: 5.1k DNP(带电源版); R_0603_1608Metric; not fitted
R9, R10: 27R; R_0603_1608Metric
R50: 30k; R_0603_1608Metric
U8: RP2040; QFN-56-1EP_7x7mm_P0.4mm_EP3.2x3.2mm
U9: W25Q128JVSIQ; SOIC-8_5.3x5.3mm_P1.27mm
Y1: 12MHz CL=10pF ABM8-272-T3; Crystal_SMD_3225-4Pin_3.2x2.5mm

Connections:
3V3_DIG: C22.1, C23.1, C24.1, C25.1, C26.1, C27.1, C84.1, C85.1, C86.1, R5.1, R6.1, U8.1 (IOVDD), U8.10 (IOVDD), U8.22 (IOVDD), U8.33 (IOVDD), U8.42 (IOVDD), U8.43 (ADC_AVDD), U8.44 (VREG_VIN), U8.48 (USB_VDD), U8.49 (IOVDD), U9.8 (VCC); also elsewhere on the board
ADSB_RXD: U8.3 (GPIO1); also elsewhere on the board
ADSB_TXD: U8.2 (GPIO0); also elsewhere on the board
ANT_SEL_1090_A: U8.6 (GPIO4); also elsewhere on the board
ANT_SEL_1090_B: U8.7 (GPIO5); also elsewhere on the board
ANT_SEL_GNSS_A: U8.8 (GPIO6); also elsewhere on the board
ANT_SEL_GNSS_B: U8.9 (GPIO7); also elsewhere on the board
BIAS_EN_978: U8.5 (GPIO3); also elsewhere on the board
BIAS_EN_1090: U8.4 (GPIO2); also elsewhere on the board
DEMOD0: J11.14, U8.31 (GPIO20)
DEMOD1: J11.16, U8.32 (GPIO21)
DEMOD2: J11.18, U8.34 (GPIO22)
DEMOD3: J11.17, U8.35 (GPIO23)
GND: C19.2, C20.2, C22.2, C23.2, C24.2, C25.2, C26.2, C27.2, C28.2, C29.2, C82.2, C83.2, C84.2, C85.2, C86.2, C87.2, D4.2 (A2), D5.2 (A2), J4.A1 (GND), J4.A12 (GND), J4.B1 (GND), J4.B12 (GND), J4.SH (SHIELD), J11.5, J11.7, J11.15, R7.2, R8.2, R51.2, U8.19 (TESTEN), U8.57 (GND), U9.4 (GND), Y1.2 (G), Y1.4 (G); also elsewhere on the board
LEVEL_BIAS: U8.38 (GPIO26/ADC0); also elsewhere on the board
PULSES: J11.20, U8.30 (GPIO19); also elsewhere on the board
QSPI_SCLK: U8.52 (QSPI_SCLK), U9.6 (CLK)
QSPI_SD0: U8.53 (QSPI_SD0), U9.5 (DI/IO_{0})
QSPI_SD1: U8.55 (QSPI_SD1), U9.2 (DO/IO_{1})
QSPI_SD2: U8.54 (QSPI_SD2), U9.3 (~WP/IO_{2})
QSPI_SD3: U8.51 (QSPI_SD3), U9.7 (~HOLD/~RESET/IO_{3})
QSPI_SS: J11.8, R6.2, U8.56 (~QSPI_SS), U9.1 (~CS)
RECOVERED_CLK: J11.19, U8.36 (GPIO24)
RP_1V1: C28.1, C29.1, C82.1, C83.1, U8.23 (DVDD), U8.45 (VREG_VOUT), U8.50 (DVDD)
RP_RUN: J11.6, R5.2, U8.26 (RUN)
RP_USB_DM: R10.1, U8.46 (USB_DM)
RP_USB_DP: R9.1, U8.47 (USB_DP)
RP_XIN: C19.1, U8.20 (XIN), Y1.1
RP_XOUT: R4.1, U8.21 (XOUT)
RP_XT2: C20.1, R4.2, Y1.3
RSSI: U8.39 (GPIO27/ADC1); also elsewhere on the board
SUBG_CSN: U8.16 (GPIO13); also elsewhere on the board
SUBG_IRQ: U8.17 (GPIO14); also elsewhere on the board
SUBG_MISO: U8.15 (GPIO12); also elsewhere on the board
SUBG_MOSI: U8.14 (GPIO11); also elsewhere on the board
SUBG_RESET: J11.13, U8.29 (GPIO18); also elsewhere on the board
SUBG_SCK: U8.13 (GPIO10); also elsewhere on the board
SUBG_SYNC: U8.18 (GPIO15); also elsewhere on the board
SUBG_TCKC: J11.11, U8.28 (GPIO17); also elsewhere on the board
SUBG_TMSC: J11.9, U8.27 (GPIO16); also elsewhere on the board
SWCLK: J11.10, U8.24 (SWCLK)
SWDIO: J11.12, U8.25 (SWDIO)
TL_PWM: U8.37 (GPIO25); also elsewhere on the board
USB_CC1: J4.B5 (CC2), R8.1; also elsewhere on the board
USB_CC2: J4.A5 (CC1), R7.1; also elsewhere on the board
USB_DM: D5.1 (A1), J4.A7 (D-), J4.B7 (D-), R10.2
USB_DP: D4.1 (A1), J4.A6 (D+), J4.B6 (D+), R9.2
USB_VBUS: J4.A4 (VBUS), J4.A9 (VBUS), J4.B4 (VBUS), J4.B9 (VBUS), R50.1; also elsewhere on the board
USB_VBUS_SENSE: C87.1, R50.2, R51.1, U8.40 (GPIO28/ADC2)
VHF_AUDIO: J11.2; also elsewhere on the board
VHF_SCK: J11.3; also elsewhere on the board
VHF_SDATA: J11.4; also elsewhere on the board
VHF_TCXO_TP: J11.1; also elsewhere on the board

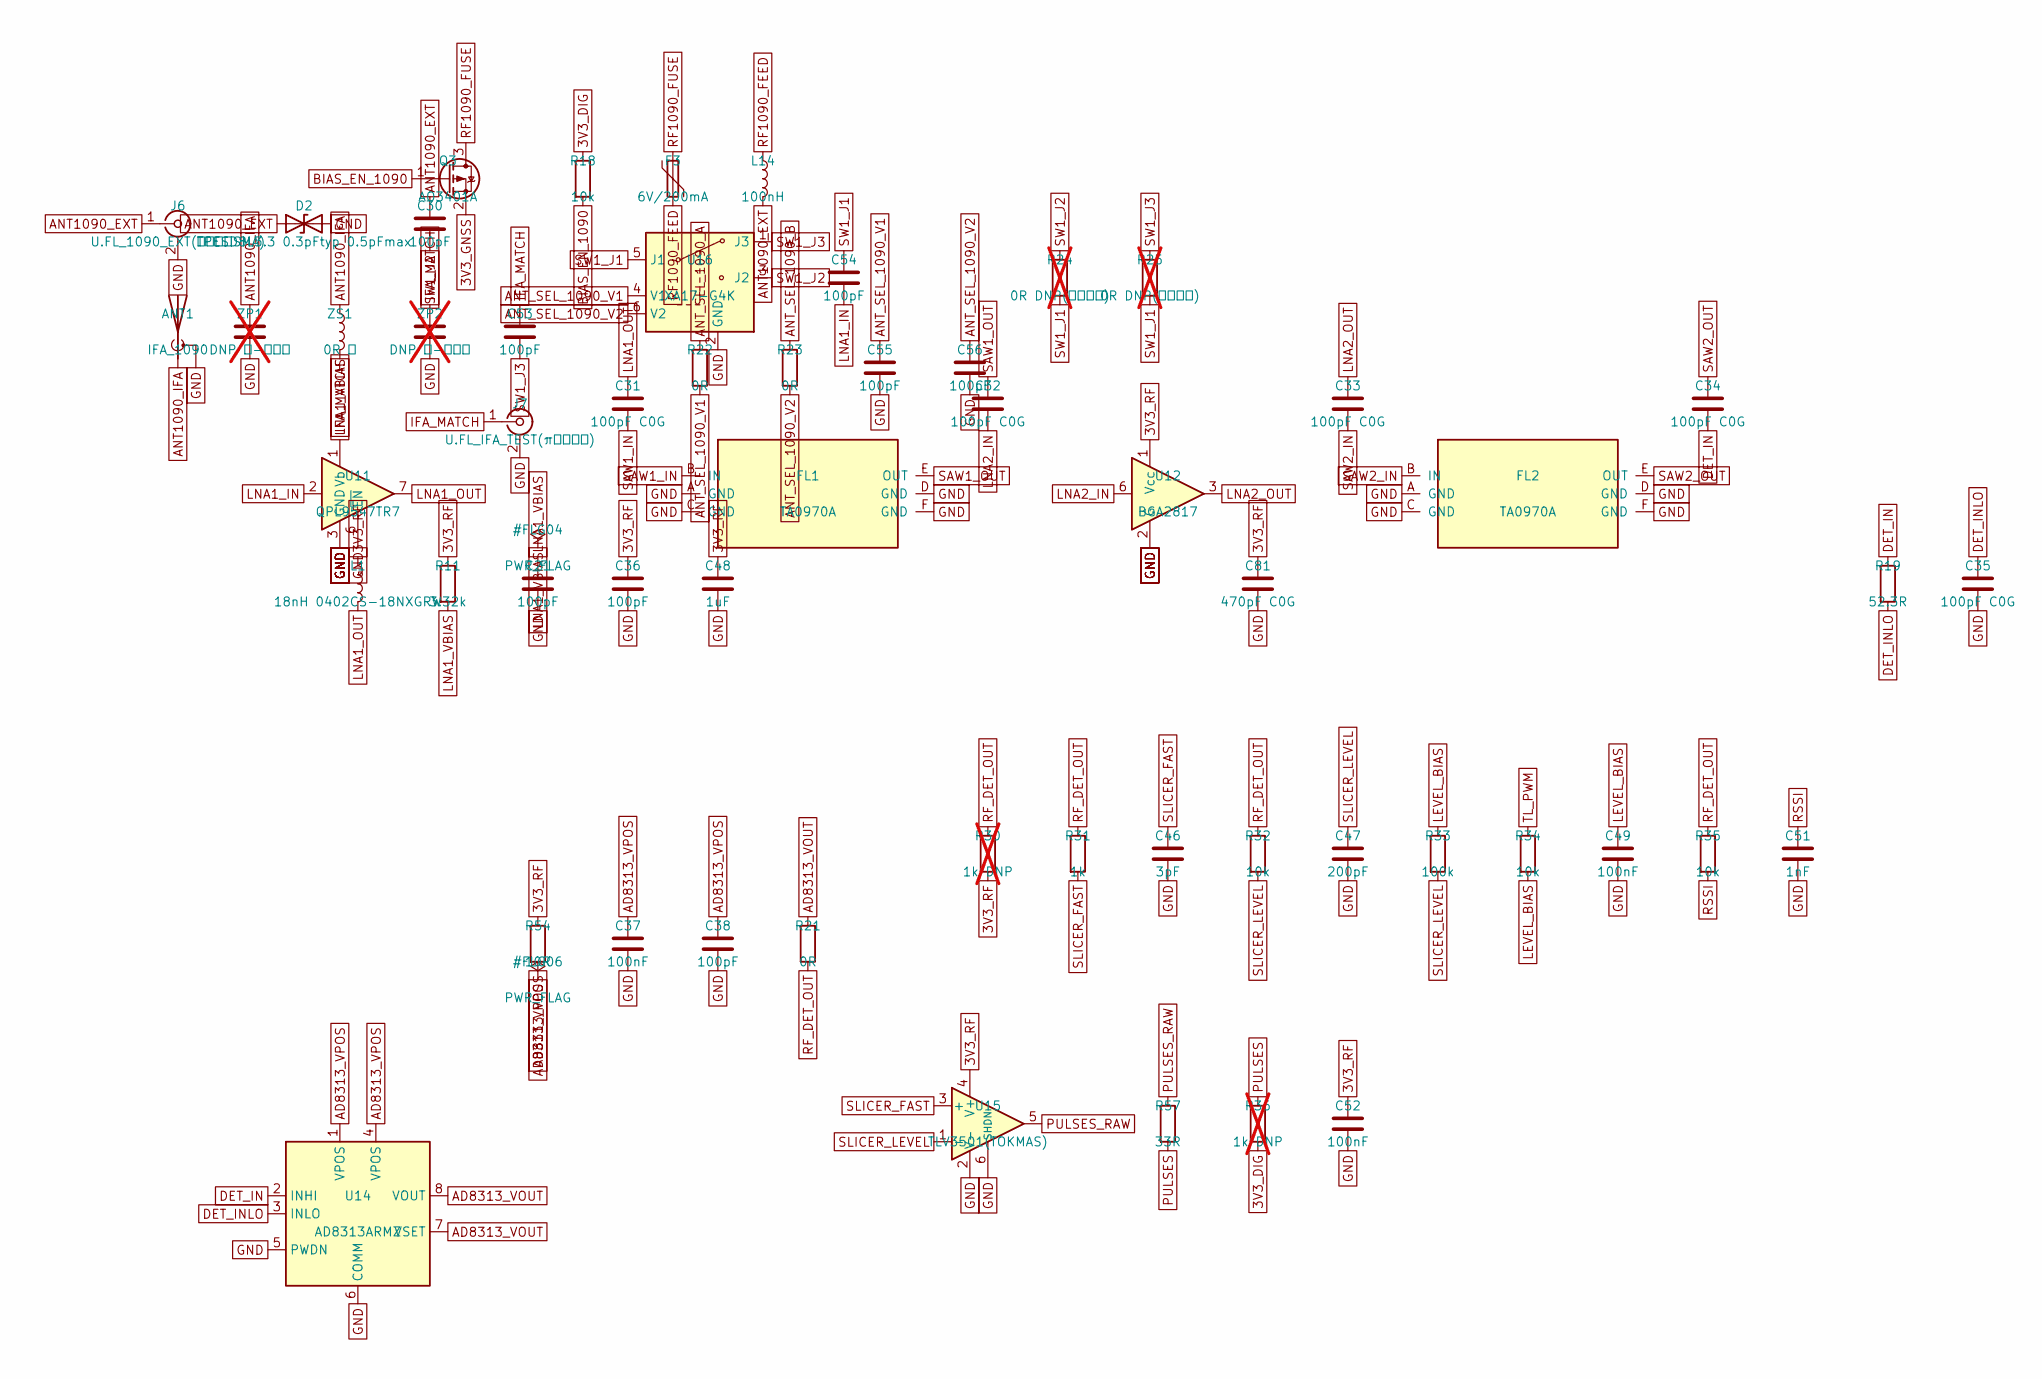
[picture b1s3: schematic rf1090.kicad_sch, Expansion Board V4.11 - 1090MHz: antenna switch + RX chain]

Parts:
ANT1: IFA_1090; ANT_IFA_1090MHz
C21, C30, C36, C38, C53, C54: 100pF; C_0402_1005Metric
C31, C32, C33, C34, C35: 100pF C0G; C_0402_1005Metric
C37, C52: 100nF; C_0402_1005Metric
C46: 3pF; C_0603_1608Metric
C47: 200pF; C_0603_1608Metric
C48: 1uF; C_0402_1005Metric
C49: 100nF; C_0603_1608Metric
C51: 1nF; C_0603_1608Metric
C55, C56: 100pF; C_0603_1608Metric
C81: 470pF C0G; C_0402_1005Metric
D2: TPESD8L3.3 0.3pFtyp 0.5pFmax; D_0402_1005Metric
F3: 6V/200mA; Fuse_0805_2012Metric
FL1, FL2: TA0970A; TA0970A_SMD3838-6
J6: U.FL_1090_EXT(经尾线转SMA); U.FL_Hirose_U.FL-R-SMT-1_Vertical
J7: U.FL_IFA_TEST(π后调试口); U.FL_Hirose_U.FL-R-SMT-1_Vertical
L1: 18nH 0402CS-18NXGRW; L_0402_1005Metric
L14: 100nH; L_0402_1005Metric
Q3: AO3401A; SOT-23
R11: 3.32k; R_0402_1005Metric
R18, R32, R34, R35: 10k; R_0603_1608Metric
R19: 52.3R; R_0402_1005Metric
R21, R22, R23: 0R; R_0603_1608Metric
R24: 0R DNP(旁路外接); R_0402_1005Metric; not fitted
R25: 0R DNP(旁路板载); R_0402_1005Metric; not fitted
R30: 1k DNP; R_0402_1005Metric; not fitted
R31: 1k; R_0603_1608Metric
R33: 100k; R_0603_1608Metric
R36: 1k DNP; R_0603_1608Metric; not fitted
R54: 10R; R_0402_1005Metric
R57: 33R; R_0603_1608Metric
U11: QPL9547TR7; DFN-8-1EP_2x2mm_P0.5mm_EP0.86x1.55mm
U12: BGA2817; SOT-363_SC-70-6
U14: AD8313ARMZ; MSOP-8_3x3mm_P0.65mm
U15: TLV3501(TOKMAS); SOT-23-6
U16: XA17-G4K; SOT-363_SC-70-6
ZP1: DNP 并-天线侧; C_0603_1608Metric; not fitted
ZP2: DNP 并-电台侧; C_0603_1608Metric; not fitted
ZS1: 0R 串; L_0603_1608Metric

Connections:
3V3_DIG: R18.1, R36.2; also elsewhere on the board
3V3_GNSS: Q3.2 (S); also elsewhere on the board
3V3_RF: C36.1, C48.1, C52.1, C81.1, L1.1, R11.1, R30.2, R54.1, U12.1 (Vcc), U15.4 (V+); also elsewhere on the board
AD8313_VOUT: R21.1, U14.7 (VSET), U14.8 (VOUT)
AD8313_VPOS: C37.1, C38.1, R54.2, U14.1 (VPOS), U14.4 (VPOS)
ANT1090_EXT: C30.1, D2.1 (A1), J6.1 (In), L14.2
ANT1090_IFA: ANT1.1 (A), ZP1.1, ZS1.1
ANT_SEL_1090_A: R22.1; also elsewhere on the board
ANT_SEL_1090_B: R23.1; also elsewhere on the board
ANT_SEL_1090_V1: C55.1, R22.2, U16.4 (V1)
ANT_SEL_1090_V2: C56.1, R23.2, U16.6 (V2)
BIAS_EN_1090: Q3.1 (G), R18.2; also elsewhere on the board
DET_IN: C34.2, R19.1, U14.2 (INHI)
DET_INLO: C35.1, R19.2, U14.3 (INLO)
GND: ANT1.2 (Shield), C21.2, C35.2, C36.2, C37.2, C38.2, C46.2, C47.2, C48.2, C49.2, C51.2, C52.2, C55.2, C56.2, C81.2, D2.2 (A2), FL1.A (GND), FL1.C (GND), FL1.D (GND), FL1.F (GND), FL2.A (GND), FL2.C (GND), FL2.D (GND), FL2.F (GND), J6.2 (Ext), J7.2 (Ext), U11.3 (GND), U11.4 (GND), U11.5 (GND), U11.6 (~EN), U11.8 (GND), U11.9 (GND), U12.2 (G), U12.4 (G), U12.5 (G), U14.5 (PWDN), U14.6 (COMM), U15.2 (V-), U15.6 (SHDN), U16.2 (GND), ZP1.2, ZP2.2; also elsewhere on the board
IFA_MATCH: C53.1, J7.1 (In), ZP2.1, ZS1.2
LEVEL_BIAS: C49.1, R33.1, R34.2; also elsewhere on the board
LNA1_IN: C54.2, U11.2
LNA1_OUT: C31.1, L1.2, U11.7
LNA1_VBIAS: C21.1, R11.2, U11.1 (Vb)
LNA2_IN: C32.2, U12.6
LNA2_OUT: C33.1, U12.3
PULSES: R36.1, R57.2; also elsewhere on the board
PULSES_RAW: R57.1, U15.5
RF1090_FEED: F3.2, L14.1
RF1090_FUSE: F3.1, Q3.3 (D)
RF_DET_OUT: R21.2, R30.1, R31.1, R32.1, R35.1
RSSI: C51.1, R35.2; also elsewhere on the board
SAW1_IN: C31.2, FL1.B (IN)
SAW1_OUT: C32.1, FL1.E (OUT)
SAW2_IN: C33.2, FL2.B (IN)
SAW2_OUT: C34.1, FL2.E (OUT)
SLICER_FAST: C46.1, R31.2, U15.3 (+)
SLICER_LEVEL: C47.1, R32.2, R33.2, U15.1 (-)
SW1_J1: C54.1, R24.2, R25.2, U16.5 (J1)
SW1_J2: C30.2, R24.1, U16.3 (J2)
SW1_J3: C53.2, R25.1, U16.1 (J3)
TL_PWM: R34.1; also elsewhere on the board

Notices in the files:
README.md:
开源协议 / License:
MIT License — 完整条款见 [`LICENSE`](LICENSE)。
Full terms in [`LICENSE`](LICENSE).
硬件设计（`hardware/`）同样以 MIT 发布。其中的 KiCad 工程内嵌了 KiCad 官方库的
封装，那些库是 CC-BY-SA 4.0，但其例外条款明确允许由此制造的板子不受限制使用，
不会传染到你的硬件。
The hardware designs under `hardware/` are released under the same MIT terms.
The KiCad projects embed footprints from the KiCad standard libraries, which are
CC-BY-SA 4.0 with an exception explicitly permitting unrestricted use of boards
produced from them.
hardware/expansion-board-v4/README.md:
License / 许可:
MIT, same as the parent repository — see the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
